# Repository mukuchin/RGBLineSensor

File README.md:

RGBラインセンサ回路（EAGLE）
RGBラインセンサの回路の.schと.brdです。ホストとセンサーの2枚あります。
RGB_LineSensorの改訂版です。

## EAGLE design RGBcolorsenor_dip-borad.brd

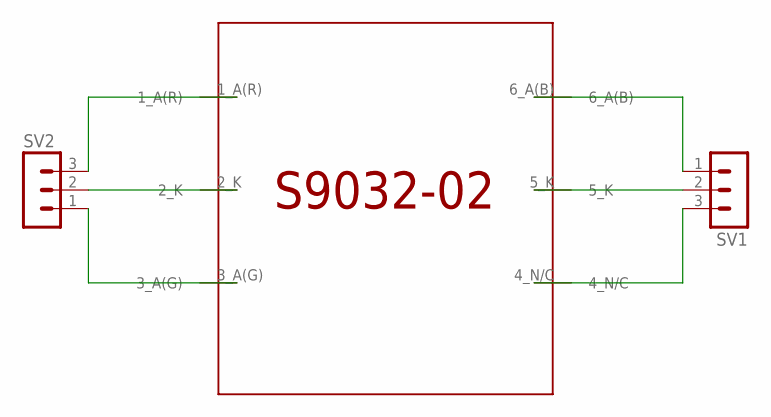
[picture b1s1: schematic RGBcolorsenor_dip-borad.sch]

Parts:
SV1, SV2: MA03-1
U$1: S9032-02

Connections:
unnamed: SV2.3, U$1.1_A(R)
unnamed: SV2.2, U$1.2_K
unnamed: SV2.1, U$1.3_A(G)
unnamed: SV1.1, U$1.6_A(B)
unnamed: SV1.2, U$1.5_K
unnamed: SV1.3, U$1.4_N/C

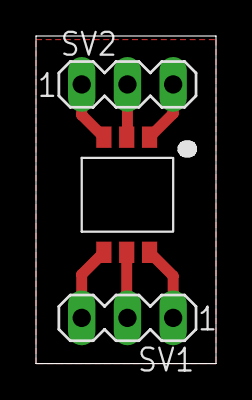
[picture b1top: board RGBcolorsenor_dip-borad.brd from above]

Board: 2 copper layers, 10.0 x 18.2 mm, 3 parts (0 on the bottom side), 6 nets.

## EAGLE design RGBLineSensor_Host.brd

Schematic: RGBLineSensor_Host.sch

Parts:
10PIN: 87758-1016
C1, C2, C3, C4, C5, C6, C7, C8, C9, C10, C11, C12, C13, C14, C15, C16, C17, C18, C19, C20, C21, C22, C23, C24: 102; C1608
C25, C57, C58: 105; C1608
C26, C27, C28, C29, C30, C31, C32, C33, C34, C35, C36, C37, C38, C39, C40, C41, C42, C43, C44, C45, C46, C47, C48, C49, C50, C51, C52, C53, C54, C55, C56: 104; C1608
IC1, IC2, IC3, IC4, IC5, IC6, IC7, IC8, IC9, IC10, IC11, IC12, IC13, IC14, IC15, IC16, IC17, IC18, IC19, IC20, IC21, IC22, IC23, IC24: NJM4580CG-TE2; SOIC127P600X175-8N
IC25, IC26, IC27: MCP3208T-BI_SL; SOIC127P600X175-16N
IC28: STM32F303K8T6; QFP80P900X900X160-32N
IC29: MCP2551-I_SN; SOIC127P600X175-8N
IC30: AP7333-33SAG-7; SOT96P240X135-3N
J1, J2, J3, J4, J5, J6, J7, J8: S3B-XH-A_LF__SN_; SHDRRA3W80P0X250_1X3_990X1150X
J9: B2B-XH-A_LF__SN_; SHDR2W64P0X250_1X2_740X575X700
LED_3V3, LED_12V: LEDCHIP-LED0603; CHIP-LED0603
LED_RX: LEDCHIP-LED0603; CHIP-LED0603
LED_TX: LEDCHIP-LED0603; CHIP-LED0603
R1, R3, R5, R7, R9, R11, R13, R15, R17, R19, R21, R23, R25, R27, R29, R31, R33, R35, R37, R39, R41, R43, R45, R47: 1M; R0603
R2, R4, R6, R8, R10, R12, R14, R16, R18, R20, R22, R24, R26, R28, R30, R32, R34, R36, R38, R40, R42, R44, R46, R48: 100; R0603
R49: 10k; R0603
R50: 33k; R0603
R51: 120; R0603
R52, R53, R54: 200; R0603
R55, R57, R58: 150; R0603
R56: 2.2k; R0603
S1: SKRPACE010; SMT(4.2X3.2)
STLINK-V2_20PIN: 87758-2016
VR1, VR2, VR3, VR4, VR5, VR6, VR7, VR8, VR9, VR10, VR11, VR12, VR13, VR14, VR15, VR16, VR17, VR18, VR19, VR20, VR21, VR22, VR23, VR24: TSR-3296W-203R; TSR3296W203R
Y1: CSTNE8M00G55Z000R0

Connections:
0V: C27.2, C28.2, C29.2, C30.2, C31.2, C32.2, C33.2, C34.2, C35.2, C36.2, C37.2, C38.2, C39.2, C40.2, C41.2, C42.2, C43.2, C44.2, C45.2, C46.2, C47.2, C48.2, C49.2, C50.2, IC1.3 (A_+INPUT), IC1.4 (V-), IC1.5 (B_+INPUT), IC2.3 (A_+INPUT), IC2.4 (V-), IC2.5 (B_+INPUT), IC3.3 (A_+INPUT), IC3.4 (V-), IC3.5 (B_+INPUT), IC4.3 (A_+INPUT), IC4.4 (V-), IC4.5 (B_+INPUT), IC5.3 (A_+INPUT), IC5.4 (V-), IC5.5 (B_+INPUT), IC6.3 (A_+INPUT), IC6.4 (V-), IC6.5 (B_+INPUT), IC7.3 (A_+INPUT), IC7.4 (V-), IC7.5 (B_+INPUT), IC8.3 (A_+INPUT), IC8.4 (V-), IC8.5 (B_+INPUT), IC9.3 (A_+INPUT), IC9.4 (V-), IC9.5 (B_+INPUT), IC10.3 (A_+INPUT), IC10.4 (V-), IC10.5 (B_+INPUT), IC11.3 (A_+INPUT), IC11.4 (V-), IC11.5 (B_+INPUT), IC12.3 (A_+INPUT), IC12.4 (V-), IC12.5 (B_+INPUT), IC13.3 (A_+INPUT), IC13.4 (V-), IC13.5 (B_+INPUT), IC14.3 (A_+INPUT), IC14.4 (V-), IC14.5 (B_+INPUT), IC15.3 (A_+INPUT), IC15.4 (V-), IC15.5 (B_+INPUT), IC16.3 (A_+INPUT), IC16.4 (V-), IC16.5 (B_+INPUT), IC17.3 (A_+INPUT), IC17.4 (V-), IC17.5 (B_+INPUT), IC18.3 (A_+INPUT), IC18.4 (V-), IC18.5 (B_+INPUT), IC19.3 (A_+INPUT), IC19.4 (V-), IC19.5 (B_+INPUT), IC20.3 (A_+INPUT), IC20.4 (V-), IC20.5 (B_+INPUT), IC21.3 (A_+INPUT), IC21.4 (V-), IC21.5 (B_+INPUT), IC22.3 (A_+INPUT), IC22.4 (V-), IC22.5 (B_+INPUT), IC23.3 (A_+INPUT), IC23.4 (V-), IC23.5 (B_+INPUT), IC24.3 (A_+INPUT), IC24.4 (V-), IC24.5 (B_+INPUT), VR1.3 (CW), VR2.3 (CW), VR3.3 (CW), VR4.3 (CW), VR5.3 (CW), VR6.3 (CW), VR7.3 (CW), VR8.3 (CW), VR9.3 (CW), VR10.3 (CW), VR11.3 (CW), VR12.3 (CW), VR13.3 (CW), VR14.3 (CW), VR15.3 (CW), VR16.3 (CW), VR17.3 (CW), VR18.3 (CW), VR19.3 (CW), VR20.3 (CW), VR21.3 (CW), VR22.3 (CW), VR23.3 (CW), VR24.3 (CW)
3V3: C25.2, C26.2, C51.1, C52.1, C53.1, C55.1, C57.2, IC25.15 (VREF), IC25.16 (VDD), IC26.15 (VREF), IC26.16 (VDD), IC27.15 (VREF), IC27.16 (VDD), IC28.1 (VDD_1), IC28.5 (VDDA/VREF+), IC28.17 (VDD_2), R55.1, STLINK-V2_20PIN.1, STLINK-V2_20PIN.2
5V: 10PIN.9, 10PIN.10, C56.2, C58.2, IC29.3 (VDD), J9.2
12V: 10PIN.1, 10PIN.2, C27.1, C28.1, C29.1, C30.1, C31.1, C32.1, C33.1, C34.1, C35.1, C36.1, C37.1, C38.1, C39.1, C40.1, C41.1, C42.1, C43.1, C44.1, C45.1, C46.1, C47.1, C48.1, C49.1, C50.1, IC1.8 (V+), IC2.8 (V+), IC3.8 (V+), IC4.8 (V+), IC5.8 (V+), IC6.8 (V+), IC7.8 (V+), IC8.8 (V+), IC9.8 (V+), IC10.8 (V+), IC11.8 (V+), IC12.8 (V+), IC13.8 (V+), IC14.8 (V+), IC15.8 (V+), IC16.8 (V+), IC17.8 (V+), IC18.8 (V+), IC19.8 (V+), IC20.8 (V+), IC21.8 (V+), IC22.8 (V+), IC23.8 (V+), IC24.8 (V+), R56.1
CAN_H: 10PIN.5, IC29.7 (CANH), R51.2
CAN_L: 10PIN.6, IC29.6 (CANL), R51.1
CLK: IC25.13 (CLK), IC26.13 (CLK), IC27.13 (CLK), IC28.11 (PA5)
CS_B: IC27.10 (!CS!/SHDN), IC28.8 (PA2)
CS_G: IC25.10 (!CS!/SHDN), IC28.6 (PA0)
CS_R: IC26.10 (!CS!/SHDN), IC28.7 (PA1)
GND: 10PIN.7, 10PIN.8, C25.1, C26.1, C51.2, C52.2, C53.2, C54.2, C55.2, C56.1, IC25.9 (DGND), IC25.14 (AGND), IC26.9 (DGND), IC26.14 (AGND), IC27.9 (DGND), IC27.14 (AGND), IC28.16 (VSS_2), IC28.32 (VSS_1), IC29.2 (VSS), IC30.3 (GND), J9.1, LED_3V3.C, LED_12V.C, LED_RX.C, LED_TX.C, R49.2, R50.2, S1.4, STLINK-V2_20PIN.4, STLINK-V2_20PIN.7, STLINK-V2_20PIN.9, STLINK-V2_20PIN.11, STLINK-V2_20PIN.13, STLINK-V2_20PIN.17, STLINK-V2_20PIN.19, Y1.2 (GND)
LED_RX: IC28.14 (PB0), R57.1
LED_TX: IC28.15 (PB1), R58.1
MISO: IC25.12 (DOUT), IC26.12 (DOUT), IC27.12 (DOUT), IC28.12 (PA6)
MOSI: IC25.11 (DIN), IC26.11 (DIN), IC27.11 (DIN), IC28.13 (PA7)
unnamed: C1.1, IC1.2 (A_-INPUT), J1.3, R1.2
unnamed: C57.1, IC30.2 (OUT)
unnamed: C1.2, IC1.1 (A_OUTPUT), R1.1, R2.1
unnamed: C7.1, IC7.2 (A_-INPUT), J3.3, R13.2
unnamed: IC1.6 (B_-INPUT), R2.2, VR1.1 (CW1)
unnamed: IC28.22 (PA12), IC29.1 (TXD)
unnamed: C2.2, IC2.1 (A_OUTPUT), R3.1, R4.1
unnamed: C2.1, IC2.2 (A_-INPUT), J1.2, R3.2
unnamed: IC2.6 (B_-INPUT), R4.2, VR2.1 (CW1)
unnamed: IC28.21 (PA11), IC29.4 (RXD)
unnamed: C3.2, IC3.1 (A_OUTPUT), R5.1, R6.1
unnamed: C7.2, IC7.1 (A_OUTPUT), R13.1, R14.1
unnamed: IC3.6 (B_-INPUT), R6.2, VR3.1 (CW1)
unnamed: IC29.8 (RS), R50.1
unnamed: C4.1, IC4.2 (A_-INPUT), J2.3, R7.2
unnamed: C3.1, IC3.2 (A_-INPUT), J1.1, R5.2
unnamed: C4.2, IC4.1 (A_OUTPUT), R7.1, R8.1
unnamed: IC6.6 (B_-INPUT), R12.2, VR6.1 (CW1)
unnamed: IC10.6 (B_-INPUT), R20.2, VR10.1 (CW1)
unnamed: IC8.6 (B_-INPUT), R16.2, VR8.1 (CW1)
unnamed: IC9.6 (B_-INPUT), R18.2, VR9.1 (CW1)
unnamed: IC11.6 (B_-INPUT), R22.2, VR11.1 (CW1)
unnamed: IC13.6 (B_-INPUT), R26.2, VR13.1 (CW1)
unnamed: IC24.6 (B_-INPUT), R48.2, VR24.1 (CW1)
unnamed: C5.1, IC5.2 (A_-INPUT), J2.2, R9.2
unnamed: C5.2, IC5.1 (A_OUTPUT), R9.1, R10.1
unnamed: IC14.6 (B_-INPUT), R28.2, VR14.1 (CW1)
unnamed: IC16.6 (B_-INPUT), R32.2, VR16.1 (CW1)
unnamed: IC5.6 (B_-INPUT), R10.2, VR5.1 (CW1)
unnamed: IC18.6 (B_-INPUT), R36.2, VR18.1 (CW1)
unnamed: IC15.6 (B_-INPUT), R30.2, VR15.1 (CW1)
unnamed: IC23.6 (B_-INPUT), R46.2, VR23.1 (CW1)
unnamed: C6.2, IC6.1 (A_OUTPUT), R11.1, R12.1
unnamed: IC21.6 (B_-INPUT), R42.2, VR21.1 (CW1)
unnamed: C24.1, IC24.2 (A_-INPUT), J8.1, R47.2
unnamed: IC28.31 (BOOT0), R49.1
unnamed: C6.1, IC6.2 (A_-INPUT), J2.1, R11.2
unnamed: R52.1, Y1.3 (OUTPUT)
unnamed: IC22.6 (B_-INPUT), R44.2, VR22.1 (CW1)
unnamed: C24.2, IC24.1 (A_OUTPUT), R47.1, R48.1
unnamed: C8.1, IC8.2 (A_-INPUT), J3.2, R15.2
unnamed: C8.2, IC8.1 (A_OUTPUT), R15.1, R16.1
unnamed: C9.2, IC9.1 (A_OUTPUT), R17.1, R18.1
unnamed: IC17.6 (B_-INPUT), R34.2, VR17.1 (CW1)
unnamed: C58.1, IC30.1 (IN)
unnamed: C22.2, IC22.1 (A_OUTPUT), R43.1, R44.1
unnamed: LED_3V3.A, R55.2
unnamed: R52.2, R53.1
unnamed: C9.1, IC9.2 (A_-INPUT), J3.1, R17.2
unnamed: IC4.6 (B_-INPUT), R8.2, VR4.1 (CW1)
unnamed: C10.1, IC10.2 (A_-INPUT), J4.3, R19.2
unnamed: IC19.6 (B_-INPUT), R38.2, VR19.1 (CW1)
unnamed: R53.2, R54.1
unnamed: C10.2, IC10.1 (A_OUTPUT), R19.1, R20.1
unnamed: IC28.3 (PF1/OSC_OUT), R54.2
unnamed: C11.1, IC11.2 (A_-INPUT), J4.2, R21.2
unnamed: C11.2, IC11.1 (A_OUTPUT), R21.1, R22.1
unnamed: IC20.6 (B_-INPUT), R40.2, VR20.1 (CW1)
unnamed: IC28.2 (PF0/OSC_IN), Y1.1 (INPUT)
unnamed: IC12.6 (B_-INPUT), R24.2, VR12.1 (CW1)
unnamed: IC7.6 (B_-INPUT), R14.2, VR7.1 (CW1)
unnamed: C12.2, IC12.1 (A_OUTPUT), R23.1, R24.1
unnamed: LED_12V.A, R56.2
unnamed: C16.1, IC16.2 (A_-INPUT), J6.3, R31.2
unnamed: C13.1, IC13.2 (A_-INPUT), J5.3, R25.2
unnamed: C13.2, IC13.1 (A_OUTPUT), R25.1, R26.1
unnamed: C12.1, IC12.2 (A_-INPUT), J4.1, R23.2
unnamed: C14.1, IC14.2 (A_-INPUT), J5.2, R27.2
unnamed: LED_RX.A, R57.2
unnamed: C14.2, IC14.1 (A_OUTPUT), R27.1, R28.1
unnamed: C15.1, IC15.2 (A_-INPUT), J5.1, R29.2
unnamed: LED_TX.A, R58.2
unnamed: C15.2, IC15.1 (A_OUTPUT), R29.1, R30.1
unnamed: C16.2, IC16.1 (A_OUTPUT), R31.1, R32.1
unnamed: C17.1, IC17.2 (A_-INPUT), J6.2, R33.2
unnamed: C17.2, IC17.1 (A_OUTPUT), R33.1, R34.1
unnamed: C19.1, IC19.2 (A_-INPUT), J7.3, R37.2
unnamed: C18.2, IC18.1 (A_OUTPUT), R35.1, R36.1
unnamed: C18.1, IC18.2 (A_-INPUT), J6.1, R35.2
unnamed: C19.2, IC19.1 (A_OUTPUT), R37.1, R38.1
unnamed: C20.1, IC20.2 (A_-INPUT), J7.2, R39.2
unnamed: C20.2, IC20.1 (A_OUTPUT), R39.1, R40.1
unnamed: C21.2, IC21.1 (A_OUTPUT), R41.1, R42.1
unnamed: C21.1, IC21.2 (A_-INPUT), J7.1, R41.2
unnamed: C23.1, IC23.2 (A_-INPUT), J8.2, R45.2
unnamed: C23.2, IC23.1 (A_OUTPUT), R45.1, R46.1
unnamed: C22.1, IC22.2 (A_-INPUT), J8.3, R43.2
NRST: C54.1, IC28.4 (NRST), S1.2, STLINK-V2_20PIN.16
SIGNAL_B0: IC3.7 (B_OUTPUT), IC27.1 (CH0), VR3.2 (WIPER)
SIGNAL_B1: IC6.7 (B_OUTPUT), IC27.2 (CH1), VR6.2 (WIPER)
SIGNAL_B2: IC9.7 (B_OUTPUT), IC27.3 (CH2), VR9.2 (WIPER)
SIGNAL_B3: IC12.7 (B_OUTPUT), IC27.4 (CH3), VR12.2 (WIPER)
SIGNAL_B4: IC15.7 (B_OUTPUT), IC27.5 (CH4), VR15.2 (WIPER)
SIGNAL_B5: IC18.7 (B_OUTPUT), IC27.6 (CH5), VR18.2 (WIPER)
SIGNAL_B6: IC21.7 (B_OUTPUT), IC27.7 (CH6), VR21.2 (WIPER)
SIGNAL_B7: IC24.7 (B_OUTPUT), IC27.8 (CH7), VR24.2 (WIPER)
SIGNAL_G0: IC1.7 (B_OUTPUT), IC25.1 (CH0), VR1.2 (WIPER)
SIGNAL_G1: IC4.7 (B_OUTPUT), IC25.2 (CH1), VR4.2 (WIPER)
SIGNAL_G2: IC7.7 (B_OUTPUT), IC25.3 (CH2), VR7.2 (WIPER)
SIGNAL_G3: IC10.7 (B_OUTPUT), IC25.4 (CH3), VR10.2 (WIPER)
SIGNAL_G4: IC13.7 (B_OUTPUT), IC25.5 (CH4), VR13.2 (WIPER)
SIGNAL_G5: IC16.7 (B_OUTPUT), IC25.6 (CH5), VR16.2 (WIPER)
SIGNAL_G6: IC19.7 (B_OUTPUT), IC25.7 (CH6), VR19.2 (WIPER)
SIGNAL_G7: IC22.7 (B_OUTPUT), IC25.8 (CH7), VR22.2 (WIPER)
SIGNAL_R0: IC2.7 (B_OUTPUT), IC26.1 (CH0), VR2.2 (WIPER)
SIGNAL_R1: IC5.7 (B_OUTPUT), IC26.2 (CH1), VR5.2 (WIPER)
SIGNAL_R2: IC8.7 (B_OUTPUT), IC26.3 (CH2), VR8.2 (WIPER)
SIGNAL_R3: IC11.7 (B_OUTPUT), IC26.4 (CH3), VR11.2 (WIPER)
SIGNAL_R4: IC14.7 (B_OUTPUT), IC26.5 (CH4), VR14.2 (WIPER)
SIGNAL_R5: IC17.7 (B_OUTPUT), IC26.6 (CH5), VR17.2 (WIPER)
SIGNAL_R6: IC20.7 (B_OUTPUT), IC26.7 (CH6), VR20.2 (WIPER)
SIGNAL_R7: IC23.7 (B_OUTPUT), IC26.8 (CH7), VR23.2 (WIPER)
SWCLK: STLINK-V2_20PIN.10
SWDIO: STLINK-V2_20PIN.8
VCP_RX: IC28.25 (PA15), STLINK-V2_20PIN.5
VCP_TX: IC28.24 (PA14), STLINK-V2_20PIN.3

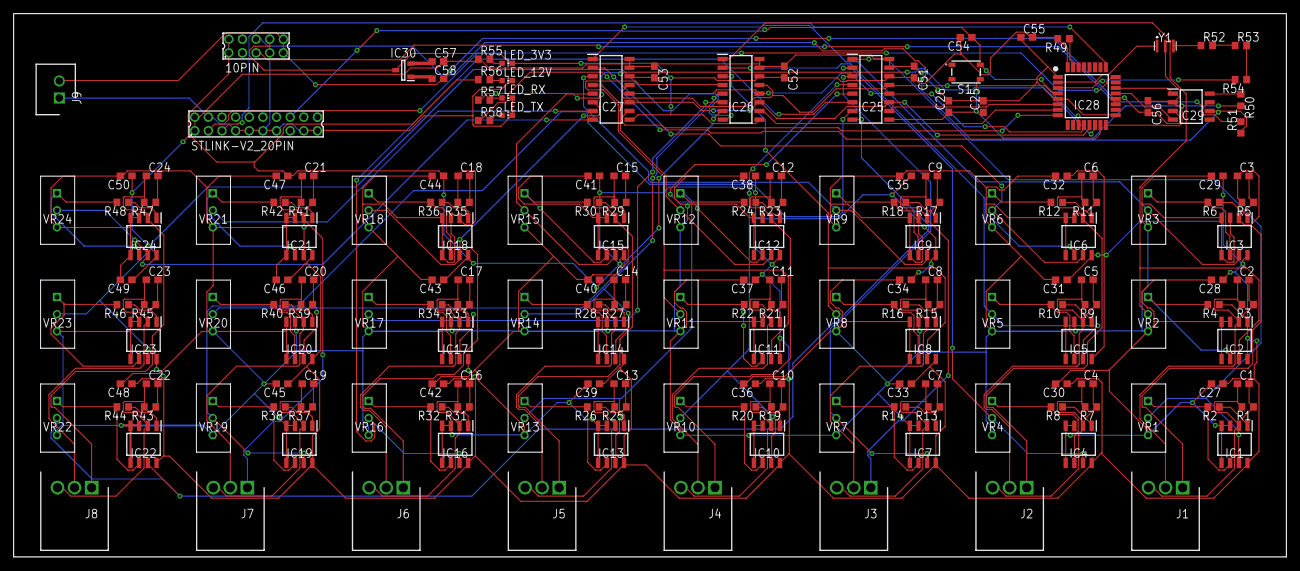
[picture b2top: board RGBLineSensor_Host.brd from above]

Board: 2 copper layers, 186.7 x 79.7 mm, 187 parts (0 on the bottom side), 129 nets.

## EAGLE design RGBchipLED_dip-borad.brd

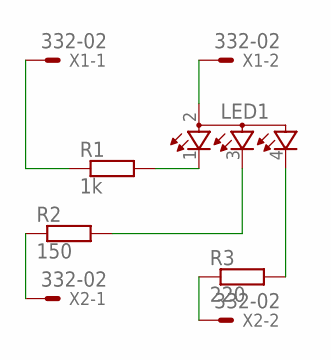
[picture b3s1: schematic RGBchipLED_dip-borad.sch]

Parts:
LED1: TOPLED-3; P-LCC-4-3
R1: 1k; SMK
R2: 150; SMK
R3: 220; SMK
X1, X2: 332-02

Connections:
unnamed: R1.2, X1.1
unnamed: LED1.2 (A2), X1.2
unnamed: R2.2, X2.1
unnamed: LED1.4 (CGREEN), R3.1
unnamed: LED1.3 (CBLUE), R2.1
unnamed: R3.2, X2.2
unnamed: LED1.1 (CRED), R1.1

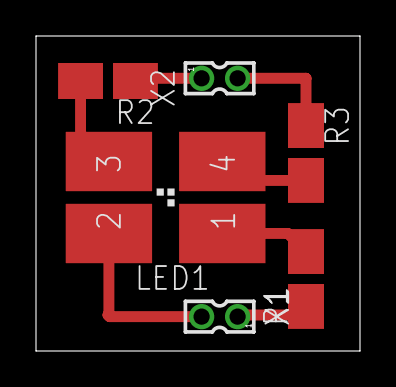
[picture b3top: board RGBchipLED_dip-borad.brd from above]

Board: 2 copper layers, 18.0 x 17.5 mm, 6 parts (0 on the bottom side), 7 nets.

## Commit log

2020-10-03 RGBラインセンサ基盤
2020-10-03 部品の位置をちょっと変えました
